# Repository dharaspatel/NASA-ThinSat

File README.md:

# NASA-ThinSat
---

This GitHub is a collection of 1) pcb design and logic 2) location determination 3) event triggering for mission NG13. 3 satellites will be launched - Joe Loftus, Burt Cour-Palais, Bill Rochelle. For more detail, see the GitHub Wiki.

--- 
## Joe Loftus 

Joe (also named *Cosmic DC*) has an Atmega, clock, power, and downlink capability. It keeps track of time to trigger melt wires to activate launchers and pyrolysis.

---
## Burt Cour-Palais

Burt (also named *Lt. Surge*) executes pyrolysis and launches the 4 launchers at the command of Joe. It also collects data on pyrolysis using the temperature sensor and CMOS image sensor.

---
## Bill Rochelle

Bill (also named *Fall Out Boy*), unlike Burt, has its own clock, Atmega, and downlink capability. In the next mission Bill will prove it *can* deorbit by executing all protocalls without propelant to deorbit.

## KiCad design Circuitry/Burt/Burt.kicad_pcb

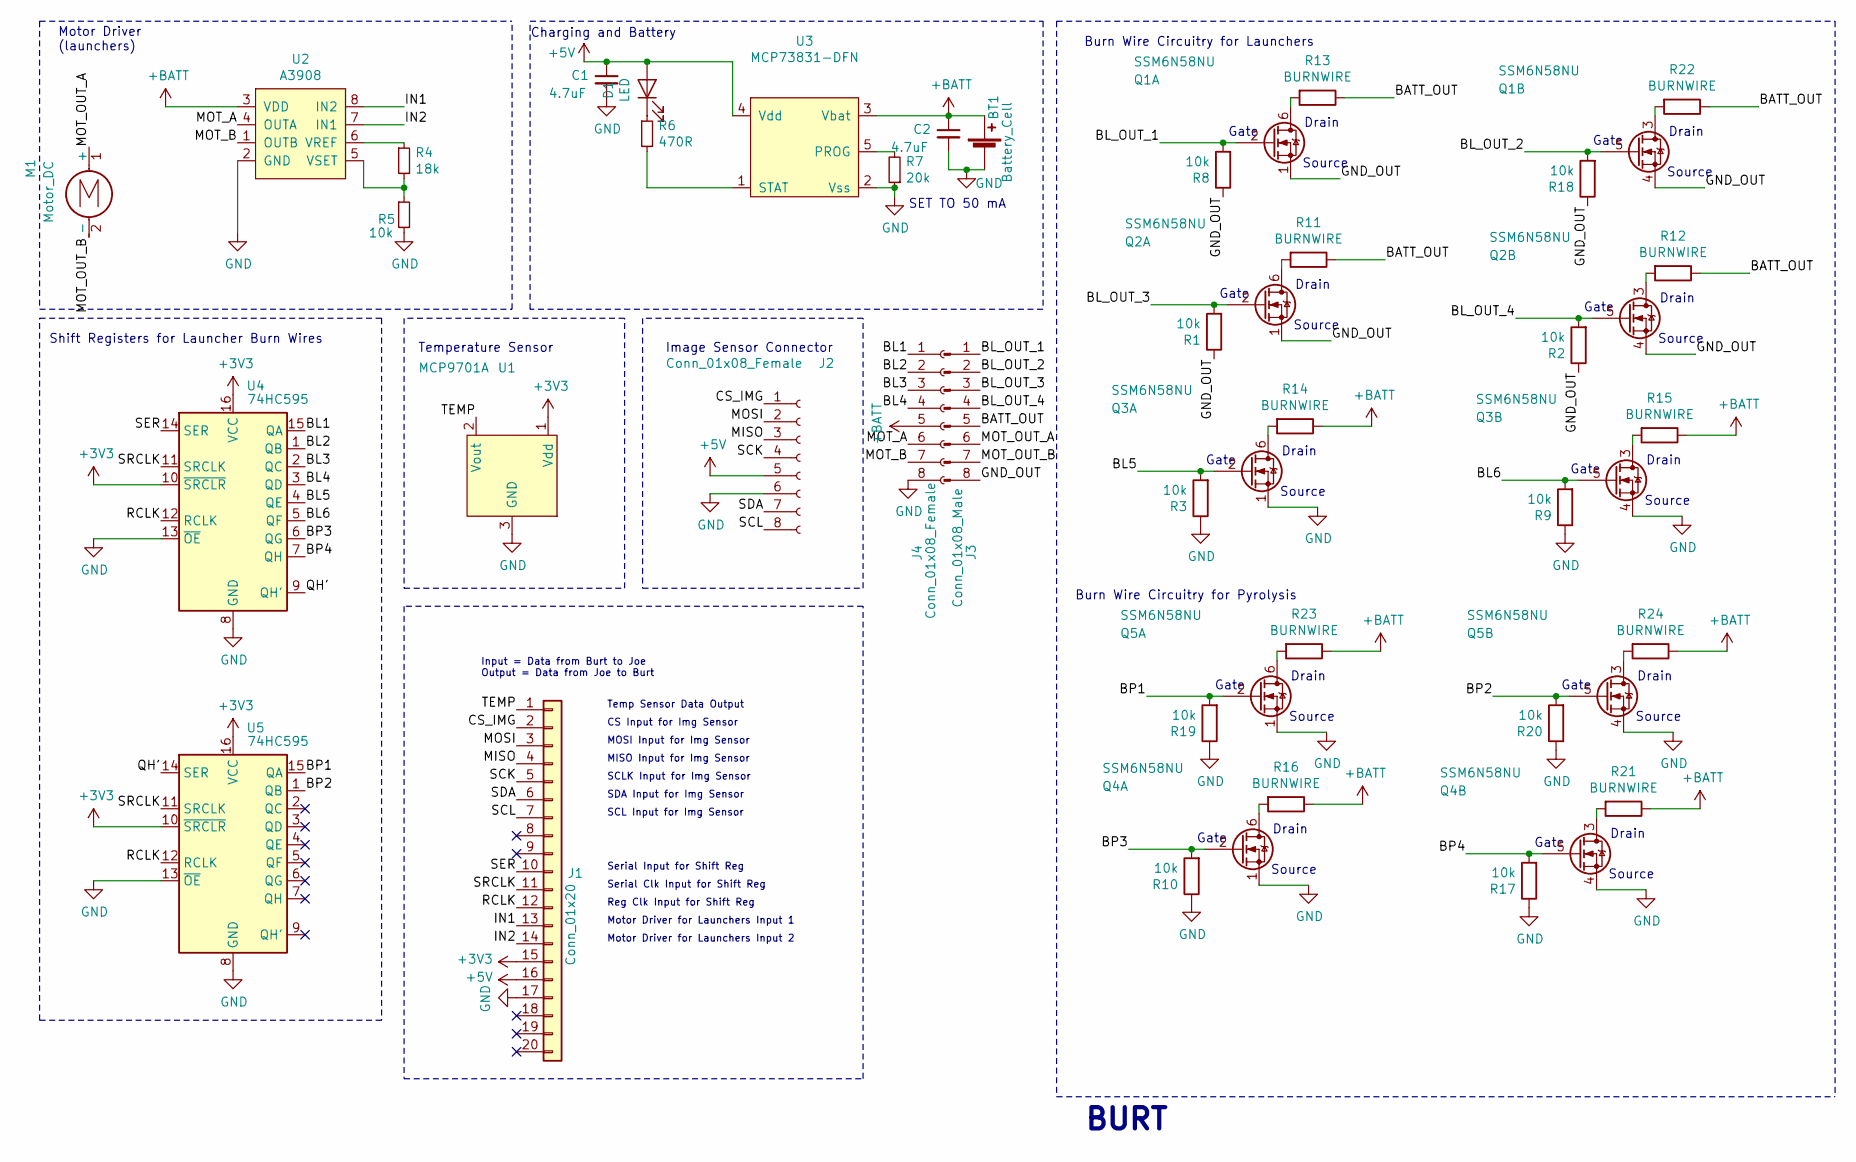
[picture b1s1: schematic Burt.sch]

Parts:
BT1: Battery_Cell; JST_PH_B2B-PH-K_1x02_P2.00mm_Vertical
C1, C2: 4.7uF; C_0603_1608Metric
D1: LED; LED_0603_1608Metric
J1: Conn_01x20; 62674-201121ALF
J2: Conn_01x08_Female; PinHeader_1x08_P2.54mm_Horizontal
J3: Conn_01x08_Male; PinHeader_1x08_P1.00mm_Vertical
J4: Conn_01x08_Female; PinHeader_1x08_P1.00mm_Vertical
M1: Motor_DC; JST_PH_B2B-PH-K_1x02_P2.00mm_Vertical
Q1, Q2, Q3, Q4, Q5: SSM6N58NU; DFN-6-1EP_2x2mm_P0.65mm_EP1x1.6mm
R1, R2, R3, R5, R8, R9, R10, R17, R18, R19, R20: 10k; R_0603_1608Metric
R4: 18k; R_0603_1608Metric
R6: 470R; R_0603_1608Metric
R7: 20k; R_0603_1608Metric
R11, R12, R13, R14, R15, R16, R21, R22, R23, R24: BURNWIRE; PinHeader_1x02_P1.00mm_Vertical
U1: MCP9701A; SOT-23
U2: A3908
U3: MCP73831-DFN; SOT-23-5
U4, U5: 74HC595; SOIC-16_3.9x9.9mm_P1.27mm

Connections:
+3V3: J1.15, U1.1 (Vdd), U4.10 (~SRCLR), U4.16 (VCC), U5.10 (~SRCLR), U5.16 (VCC)
+5V: C1.1, D1.2 (A), J1.16, J2.5, U3.4 (Vdd)
+BATT: BT1.1 (+), C2.1, J4.5, R14.1, R15.1, R16.1, R21.1, R23.1, R24.1, U2.3 (VDD), U3.3 (Vbat)
/BATT_OUT: J3.5, R11.1, R12.1, R13.1, R22.1
/BL1: J4.1, U4.15 (QA)
/BL2: J4.2, U4.1 (QB)
/BL3: J4.3, U4.2 (QC)
/BL4: J4.4, U4.3 (QD)
/BL5: Q3.2 (G), R3.2, U4.4 (QE)
/BL6: Q3.5 (G), R9.2, U4.5 (QF)
/BL_OUT_1: J3.1, Q1.2 (G), R8.2
/BL_OUT_2: J3.2, Q1.5 (G), R18.2
/BL_OUT_3: J3.3, Q2.2 (G), R1.2
/BL_OUT_4: J3.4, Q2.5 (G), R2.2
/BP1: Q5.2 (G), R19.2, U5.15 (QA)
/BP2: Q5.5 (G), R20.2, U5.1 (QB)
/BP3: Q4.2 (G), R10.2, U4.6 (QG)
/BP4: Q4.5 (G), R17.2, U4.7 (QH)
/CS_IMG: J1.2, J2.1
/GND_OUT: J3.8, Q1.1 (S), Q1.4 (S), Q2.1 (S), Q2.4 (S), R1.1, R2.1, R8.1, R18.1
/IN1: J1.13, U2.8 (IN2)
/IN2: J1.14, U2.7 (IN1)
/MISO: J1.4, J2.3
/MOSI: J1.3, J2.2
/MOT_A: J4.6, U2.4 (OUTA)
/MOT_B: J4.7, U2.1 (OUTB)
/MOT_OUT_A: J3.6, M1.1 (+)
/MOT_OUT_B: J3.7, M1.2 (-)
/QH': U4.9 (QH'), U5.14 (SER)
/RCLK: J1.12, U4.12 (RCLK), U5.12 (RCLK)
/SCK: J1.5, J2.4
/SCL: J1.7, J2.8
/SDA: J1.6, J2.7
/SER: J1.10, U4.14 (SER)
/SRCLK: J1.11, U4.11 (SRCLK), U5.11 (SRCLK)
/TEMP: J1.1, U1.2 (Vout)
GND: BT1.2 (-), C1.2, C2.2, J1.17, J2.6, J4.8, Q3.1 (S), Q3.4 (S), Q4.1 (S), Q4.4 (S), Q5.1 (S), Q5.4 (S), R3.1, R5.2, R7.1, R9.1, R10.1, R17.1, R19.1, R20.1, U1.3 (GND), U2.2 (GND), U3.2 (Vss), U4.8 (GND), U4.13 (~OE), U5.8 (GND), U5.13 (~OE)
unnamed: D1.1 (K), R6.1
unnamed: Q1.3 (D), R22.2
unnamed: Q1.6 (D), R13.2
unnamed: Q2.3 (D), R12.2
unnamed: Q2.6 (D), R11.2
unnamed: Q3.3 (D), R15.2
unnamed: Q3.6 (D), R14.2
unnamed: Q4.3 (D), R21.2
unnamed: Q4.6 (D), R16.2
unnamed: Q5.3 (D), R24.2
unnamed: Q5.6 (D), R23.2
unnamed: R4.1, U2.6 (VREF)
unnamed: R4.2, R5.1, U2.5 (VSET)
unnamed: R6.2, U3.1 (STAT)
unnamed: R7.2, U3.5 (PROG)

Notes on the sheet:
BURT
Temperature Sensor
SET TO 50 mA
Charging and Battery
Motor Driver (launchers)
Image Sensor Connector
Temp Sensor Data Output
CS Input for Img Sensor
MOSI Input for Img Sensor
Serial Input for Shift Reg
Serial Clk Input for Shift Reg
Reg Clk Input for Shift Reg
Motor Driver for Launchers Input 1
Motor Driver for Launchers Input 2
Input = Data from Burt to Joe Output = Data from Joe to Burt
MISO Input for Img Sensor
SCLK Input for Img Sensor
SDA Input for Img Sensor
SCL Input for Img Sensor
Burn Wire Circuitry for Launchers
Shift Registers for Launcher Burn Wires
Source
Gate
Drain
Burn Wire Circuitry for Pyrolysis

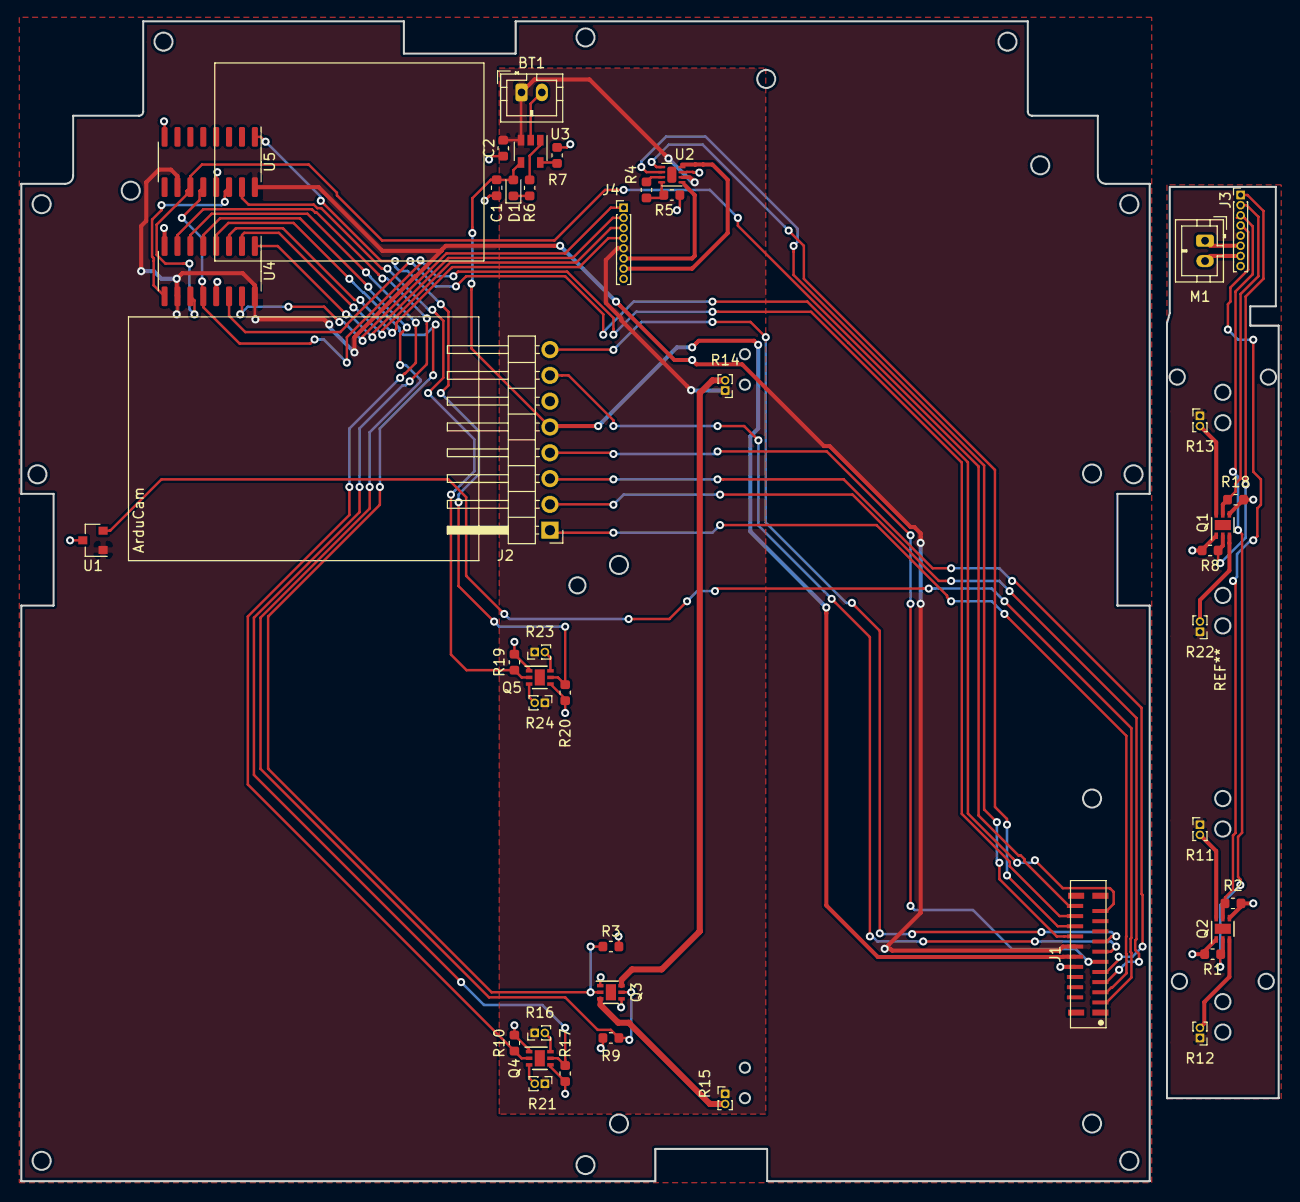
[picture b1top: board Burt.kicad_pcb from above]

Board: 2 copper layers, 123.8 x 114.2 mm, 43 parts (0 on the bottom side), 52 nets.

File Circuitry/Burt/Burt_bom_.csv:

Component,Description,Part,References,Value,Footprint,Quantity Per PCB,Datasheet,Part URL
1,Single-cell battery,Battery_Cell,BT1,Battery_Cell,JST_PH_B2B-PH-K_1x02_P2.00mm_Vertical,1,~,https://www.digikey.com/product-detail/en/jst-sales-america-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
2,"Unpolarized capacitor, small symbol",C_Small,C1 C2,4.7uF,C_0603_1608Metric,2,~,https://www.digikey.com/product-detail/en/samsung-electro-me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
3,Light emitting diode,LED,D1,LED,LED_0603_1608Metric,1,~,https://www.digikey.com/product-detail/en/lumex-opto-compone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
4,"Generic connector, single row, 01x04, script generated (kicad-library-utils/schlib/autogen/connector/)",Conn_01x04_Female,J2,Conn_01x04_Female,PinHeader_1x04_P2.54mm_Horizontal,1,~,https://www.digikey.com/product-detail/en/sullins-connector-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
5,"Generic connector, single row, 01x08, script generated (kicad-library-utils/schlib/autogen/connector/)",Conn_01x08_Female,J4,Conn_01x08_Female,PinHeader_1x08_P1.00mm_Vertical,1,~,
6,"Generic connector, single row, 01x08, script generated (kicad-library-utils/schlib/autogen/connector/)",Conn_01x08_Male,J3,Conn_01x08_Male,PinHeader_1x08_P1.00mm_Vertical,1,~,
7,"Generic connector, single row, 01x20, script generated (kicad-library-utils/schlib/autogen/connector/)",Conn_01x20,J1,Conn_01x20,62674-201121ALF,1,~,https://www.digikey.com/product-detail/en/amphenol-icc-fci/6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
8,DC Motor,Motor_DC,M1,Motor_DC,JST_PH_B2B-PH-K_1x02_P2.00mm_Vertical,1,~,https://www.pololu.com/product/4790/
9,2 N-MOSFET transistor,SSM6N58NU,Q1 Q2 Q3 Q4 Q5 Q6,SSM6N58NU,DFN-6-1EP_2x2mm_P0.65mm_EP1x1.6mm,6,,https://www.digikey.com/product-detail/en/toshiba-semiconduc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
10,Resistor,R,R1 R2 R3 R5 R8 R9 R10 R17 R18 R19 R20 R25 R27,10k,R_0603_1608Metric,13,~,https://www.digikey.com/product-detail/en/yageo/RT0603BRD071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
11,"Resistor, small symbol",R_Small,R4,18k,R_0603_1608Metric,1,~,https://www.digikey.com/product-detail/en/yageo/RT0603BRD071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
12,"Resistor, small symbol",R_Small,R7,20k,R_0603_1608Metric,1,~,https://www.digikey.com/product-detail/en/yageo/RC0603FR-072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
13,"Resistor, small symbol",R_Small,R6,470R,R_0603_1608Metric,1,~,https://www.digikey.com/product-detail/en/yageo/RC0603FR-074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
14,Resistor,R,R11 R12 R13 R14 R15 R16 R21 R22 R23 R24 R26 R28,BURNWIRE,PinHeader_1x02_P1.00mm_Vertical,12,~,
15,8-bit serial in/out Shift Register 3-State Outputs,74HC595,U4 U5,74HC595,SOIC-16_3.9x9.9mm_P1.27mm,2,http://www.ti.com/lit/ds/symlink/sn74hc595.pdf,https://www.digikey.com/product-detail/en/nexperia-usa-inc/7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
16,,A3908-Custom,U2,A3908,A3908,1,,https://www.digikey.com/product-detail/en/allegro-microsyste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
17,,MCP73831-DFN-Custom,U3,MCP73831-DFN,SOT-23-5,1,,https://www.digikey.com/product-detail/en/microchip-technolo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
18,,MCP9701A-Custom,U1,MCP9701A,SOT-23,1,http://ww1.microchip.com/downloads/en/DeviceDoc/20001942G.pdf,https://www.digikey.com/product-detail/en/microchip-technolo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





Component Groups:,18
Component Count:,48
Fitted Components:,48
Number of PCBs:,1
Total components:,48
Schematic Version:,
Schematic Date:,
PCB Variant:,['default']
BoM Date:,Tue 30 Jul 2019 11:10:57 AM EDT
Schematic Source:,/home/dpatel1/NASA-ThinSat/Circuitry/Burt/Burt.sch
KiCad Version:,Eeschema 5.1.2-f72e74a~84~ubuntu18.04.1

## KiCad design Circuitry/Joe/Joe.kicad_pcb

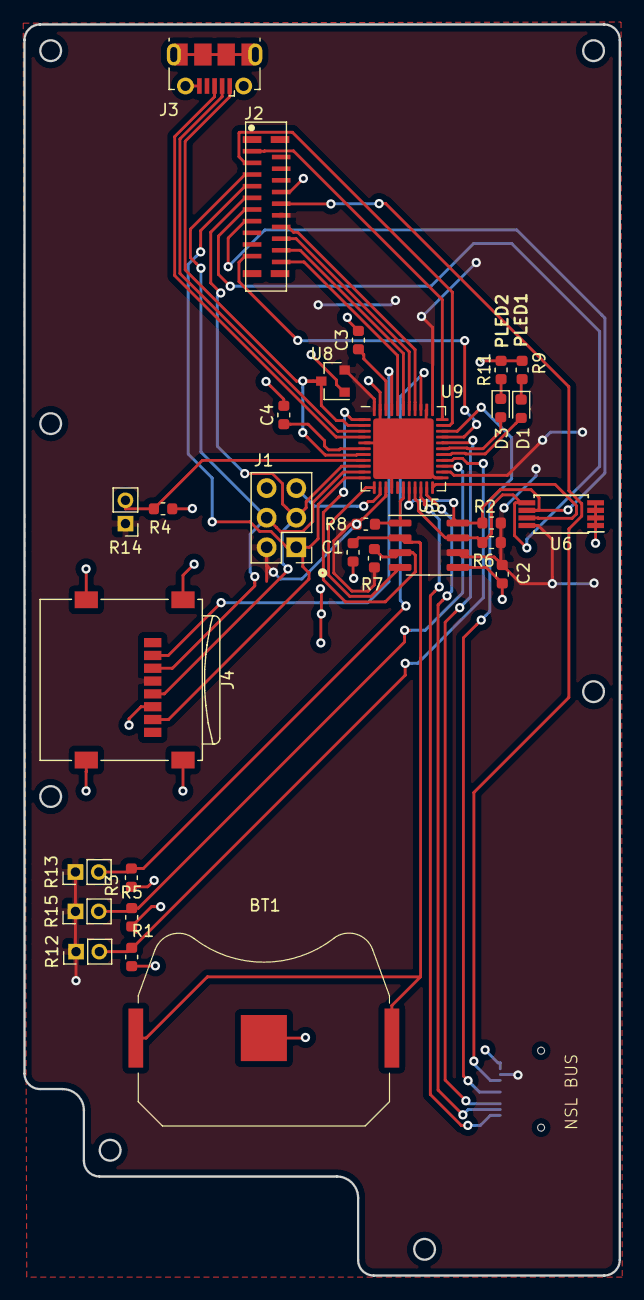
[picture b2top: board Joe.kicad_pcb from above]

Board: 2 copper layers, 51.1 x 107.3 mm, 30 parts (1 on the bottom side), 39 nets.

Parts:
BT1: Battery_Cell; BatteryHolder_Keystone_3034_1x20mm
C1, C2: 0.1uF; C_0603_1608Metric
C3, C4: 1uF; C_0603_1608Metric
D1, D3: LED; LED_0603_1608Metric
J1: Conn_02x03_Counter_Clockwise; PinHeader_2x03_P2.54mm_Vertical
J2: Conn_01x20; 62674-201121ALF
J3: USB_B_Micro; USB_Micro-B_Molex-105017-0001
J4: Micro_SD_Card; microSD_HC_Wuerth_693072010801
R1, R3, R4, R5: 1k; R_0603_1608Metric
R2, R6, R7, R8: 10k; R_0603_1608Metric
R9, R11: 440R; R_0603_1608Metric
R12, R13, R14, R15: R_PHOTO; PinHeader_1x02_P2.00mm_Vertical
U5: DS3231MZ; SOIC-8_3.9x4.9mm_P1.27mm
U6: M24C32-XDW5TP; TSSOP-8_4.4x3mm_P0.65mm
U7: DF12-20DS; DF12-20DS-0.5V(86)
U8: AP2127N-3.3; SOT-23
U9: ATmega32U4-MU; QFN-44-1EP_7x7mm_P0.5mm_EP5.2x5.2mm

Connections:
+3V3: C2.1, J1.2, J2.15, J4.4, R2.1, R6.1, R7.1, R8.1, R12.1, R13.1, R14.1, R15.1, U5.6, U6.8, U7.18, U8.2, U9.14, U9.24, U9.34, U9.44
+5V: J2.16, U7.17
/BUSY: U7.13, U9.29
/CRYSTAL: R8.2, U5.1, U9.17
/CS_IMG: J2.2, U9.32
/D+: J3.3, U9.4
/D-: J3.2, U9.3
/IN1: J2.13, U9.38
/IN2: J2.14, U9.37
/MISO: J1.1, J2.4, J4.7, U9.11
/MOSI: J1.4, J2.3, J4.3, U9.10
/PHO1: R1.1, R12.2, U9.26
/PHO2: R3.1, R13.2, U9.36
/PHO3: R4.1, R14.2, U9.8
/PHO4: R5.1, R15.2, U9.25
/PLED1: D1.2, U9.27
/PLED3: D3.2, U9.28
/RCLK: J2.12, U9.39
/RST: J1.5, U9.13
/RX: U7.12, U9.21
/SCK: J1.3, J2.5, J4.5, U9.9
/SCL: J2.7, R2.2, U5.8, U6.6, U9.18
/SDA: J2.6, R6.2, U5.7, U6.5, U9.19
/SER: J2.10, U9.30
/SQW: R7.2, U5.3, U9.1
/SRCLK: J2.11, U9.40
/STBY: U7.15, U9.31
/TEMP: J2.1, U9.33
/TMR_RST: U5.4, U9.12
/TX: U7.11, U9.20
/VBUS: J3.1, U8.3, U9.2, U9.7
/WC: U6.7, U9.22
/~CS_SD: J4.2, U9.41
GND: BT1.2, C1.2, C2.2, C3.2, C4.2, J1.6, J2.17, J3.5, J3.6, J4.6, J4.9, R1.2, R3.2, R4.2, R5.2, R9.2, R11.2, U5.5, U6.1, U6.2, U6.3, U6.4, U7.19, U7.20, U8.1, U9.5, U9.15, U9.23, U9.35, U9.43, U9.45
unnamed: BT1.1, C1.1, U5.2
unnamed: C3.1, U9.42
unnamed: C4.1, U9.6
unnamed: D1.1, R9.1
unnamed: D3.1, R11.1

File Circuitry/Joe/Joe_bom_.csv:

Component,Description,Part,References,Value,Footprint,Quantity Per PCB,Datasheet,Part URL
1,Single-cell battery,Battery_Cell,BT1,Battery_Cell,BatteryHolder_Keystone_3034_1x20mm,1,~,https://www.digikey.com/product-detail/en/keystone-electroni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
2,"Polarized capacitor, small symbol",CP_Small,C1,0.1uF,C_0603_1608Metric,1,~,https://www.digikey.com/product-detail/en/knowles-syfer/0603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
3,"Unpolarized capacitor, small symbol",C_Small,C2,0.1uF,C_0603_1608Metric,1,~,https://www.digikey.com/product-detail/en/knowles-syfer/0603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
4,Unpolarized capacitor,C,C3 C4,1uF,C_0603_1608Metric,2,~,https://www.digikey.com/product-detail/en/murata-electronics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
5,Light emitting diode,LED,D1,LED,LED_0603_1608Metric,1,~,https://www.digikey.com/product-detail/en/lite-on-inc/LTST-C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
6,"Generic connector, single row, 01x20, script generated (kicad-library-utils/schlib/autogen/connector/)",Conn_01x20,J2,Conn_01x20,62674-201121ALF,1,~,
7,"Generic connector, double row, 02x03, counter clockwise pin numbering scheme (similar to DIP packge numbering), script generated (kicad-library-utils/schlib/autogen/connector/)",Conn_02x03_Counter_Clockwise,J1,Conn_02x03_Counter_Clockwise,PinHeader_2x03_P2.54mm_Vertical,1,~,https://www.digikey.com/product-detail/en/sullins-connector-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
8,Micro SD Card Socket,Micro_SD_Card,J4,Micro_SD_Card,microSD_HC_Wuerth_693072010801,1,http://katalog.we-online.de/em/datasheet/693072010801.pdf,https://www.digikey.com/product-detail/en/wurth-electronics-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
9,USB Micro Type B connector,USB_B_Micro,J3,USB_B_Micro,USB_Micro-B_Molex-105017-0001,1,~,https://www.digikey.com/product-detail/en/molex/1050170001/W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
10,Resistor,R,R2 R6 R7 R8,10k,R_0603_1608Metric,4,~,https://www.digikey.com/product-detail/en/yageo/RT0603BRD071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
11,Resistor,R,R1 R3 R4 R5,1k,R_0603_1608Metric,4,~,https://www.digikey.com/product-detail/en/yageo/RT0603DRD071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
12,Resistor,R,R9,440R,R_0603_1608Metric,1,~,https://www.digikey.com/product-detail/en/yageo/RC0603FR-074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
13,Photoresistor,R_PHOTO,R12 R13 R14 R15,R_PHOTO,PinHeader_1x02_P2.00mm_Vertical,4,~,https://www.digikey.com/product-detail/en/advanced-photonix/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
14,"300mA low dropout linear regulator, shutdown pin, 2.5V-6V input voltage, 3.3V fixed positive output, SOT-23 package",AP2127N-3.3,U8,AP2127N-3.3,SOT-23,1,https://www.diodes.com/assets/Datasheets/AP2127.pdf,https://www.digikey.com/product-detail/en/diodes-incorporate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
15,"16MHz, 32kB Flash, 2.5kB SRAM, 1kB EEPROM, USB 2.0, QFN-44",ATmega32U4-MU,U9,ATmega32U4-MU,QFN-44-1EP_7x7mm_P0.5mm_EP5.2x5.2mm,1,http://ww1.microchip.com/downloads/en/DeviceDoc/Atmel-7766-8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,https://www.digikey.com/product-detail/en/microchip-technolo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
16,,DF12-20DS-Custom,U7,DF12-20DS,DF12-20DS-0.5V(86),1,,https://www.digikey.com/product-detail/en/hirose-electric-co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
17,"±5ppm, I2C Real-Time Clock SOIC-8",DS3231MZ,U5,DS3231MZ,SOIC-8_3.9x4.9mm_P1.27mm,1,http://datasheets.maximintegrated.com/en/ds/DS3231M.pdf,https://www.digikey.com/product-detail/en/maxim-integrated/D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
18,,UFDFPN8-MC-Custom,U6,M24C32-XDW5TP,TSSOP-8_4.4x3mm_P0.65mm,1,https://www.st.com/content/ccc/resource/technical/document/d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,https://www.digikey.com/product-detail/en/stmicroelectronics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
19,,SN74LVC1G3157DCKR,U1 U2,SN74LVC1G3157DCKR,DCK6,2,,





Component Groups:,19
Component Count:,30
Fitted Components:,30
Number of PCBs:,1
Total components:,30
Schematic Version:,
Schematic Date:,
PCB Variant:,['default']
BoM Date:,Tue 30 Jul 2019 11:13:57 AM EDT
Schematic Source:,/home/dpatel1/NASA-ThinSat/Circuitry/Joe/Joe.sch
KiCad Version:,Eeschema 5.1.2-f72e74a~84~ubuntu18.04.1

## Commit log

2019-06-12 Set up general strucutre for communicating with the payload (receiving data from sensors and sending it to the NSL Bus)
2019-06-20 organization and sensor byte addition
2019-06-24 Added spectrometer, photodiode, and atmega to sch
2019-06-27 Began writing code for electronics on Joe and Bill satellites
2019-06-28 A bit of file organization and division into Joe, Burt, Bill satellites
2019-07-01 Pinouts for sensors on burt and calc_state
2019-07-01 bus sensor pins and additional circuitry
2019-07-09 sch review changes, eeprom, linear image sensor.
2019-07-10 Complete with for-loops
2019-07-10 battery and burn wire circuitry, motor driver *incomplete
2019-07-10 motor driver
2019-07-10 burt for review
2019-07-10 Fixed symbol libraries
2019-07-10 Changed burt some
2019-07-10 changes to Joe: part lables, BW, and shift regs
2019-07-10 burt screw terminals fixed, img sensor conn
2019-07-10 screw terminal on joe
2019-07-10 Added SD card reader
2019-07-10 shift reg to burt
2019-07-10 fixed up joe
2019-07-11 Joe: RTC changed to soic8, added labels to screw terminal, removed shift regs Burt: added shift reg
2019-07-11 complete screw terminal, labeling, etc. done for FINAL REVIEW
2019-07-11 part URLs for Joe Loftus
2019-07-11 Added part URLs
2019-07-11 joe done for final review
2019-07-11 Fixed Garbage
2019-07-11 urls
2019-07-11 burt organization and screw terminal and image sensor connector
2019-07-11 fixed burn wire circuits
2019-07-12 Added custom footprint library
2019-07-12 electrical rules check ran and corrected
2019-07-12 footprints for burt
2019-07-12 Got footprints for Cosmic DC
2019-07-12 joe footprints, symbols, and sch reviewed
2019-07-12 Fixed some garbage
2019-07-15 Made a new ribbon cable connector
2019-07-15 Made cosmic dc outline
2019-07-15 joe layout
2019-07-16 completed joe layout for review; addresses for dcf
2019-07-17 Did lt surge
2019-07-17 Made pour more rectangular
2019-07-17 complete joe layoutgit add .git add .git add . woooohooooooo!
2019-07-17 functions for rtc, nsl bus, sd card, read photocells
2019-07-18 Finshed lt surge layout
2019-07-18 Moved ribbon connector
2019-07-18 planet on pcb!
2019-07-18 Sharing is caring, Emma.
    I put Emma's files into the public domain where they _belong_. Information wants to be free. Now all will know the truth.
2019-07-18 Build Lt. Surge
2019-07-18 Build zip for joe
2019-07-18 Pants are relative
    I replaced the absolute filepaths with relative ones so that other people can run it now.
2019-07-18 Keep it going
    I fixed the longitude fitting. I also changed a bunch of variable names and added comments as I was working through it.
2019-07-18 Wait… that's not even close!
    I did some analysis to find out that the current fit system gets to be over 450 km off. That's too much. I'm going to start looking into a residuals system.
2019-07-19 functions on burt
2019-07-19 bill schematic
2019-07-19 Relativity is a conspiracy
    I changed it to deal with residuals instead of absolute coordinates. The fit functions for longitude and altitude had to change. The fit still doesn't work super well. I suspect that the assumption t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
2019-07-19 Still garbage
    I gave the regression full control over all parameters. Still not a great fit. Probably because we need at least three inputs to get a semblance of linearity, and in particular, not ones that are pra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
2019-07-22 Once is enough
    I made it convert the epoch from string to datetime when it loads it instead of every time it uses it.
2019-07-22 I officially hate statsmodels
    If you want to fit a dataframe, you call statsmodels.formula.api.ols().
    If you want to fit an ndarray, you call statsmodels.api.OLS().
    This is scudding Python. What in Davy Jones's Locker is the matter with this package?
    I also changed it to fit to three dependent variables instead of two, because two wasn't enough. Give me a hot sec to make sure those independent variables are actually dece.
2019-07-23 Numpy is a gift
    I replaced all the list and things with numpy arrays to make it nicer and just a little bit faster.
2019-07-23 Eigenvectors.
    I did some informal PCA and found some values that are decently independent (read: still highly correlated) to use for predicting location. I'm going to try to fix the fitting now and see how it goes.
2019-07-23 Approximating intelligence
    The sunwend code was bugging me, so I made it better. Now, if an apparent "night" lasts fewer than 10 seconds, it will ignore it completely. It's much less error prone this way. At least in theory. W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
2019-07-23 It is remarkably nonlinear
    The word of today was validation. I wrote some new code to properly fit the estimation on a simulation that wasn't used in the regression. Turns out the phase shift and other sine parameters aren't l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
2019-07-23 image processing
2019-07-23 Splines!
    I changed the fit curves to splines. Splines are great.
2019-07-24 script to run many gmat scripts
    python script to run multiple gmat scripts with slightly different initial velocity vector
2019-07-24 GMAT script to find lat, long, alt at each sunrise
2019-07-24 You suck.
    I did some proper validation, and it turns out to actually be pretty good.
2019-07-24 Now with less cheating!
    It was using data it wouldn't actually have access to yet. Now it doesn't do that, and it still works fine.
2019-07-24 Packaged and ready to go
    It outputs a file now.
2019-07-24 I like this one better
2019-07-25 Don't trust anyone
    I changed it so that it no longer depends on the absolute accuracy of the RTC; it can guess its position given only the difference between times. Altitude is a lot harder this way, but latitude and l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
2019-07-25 Revert "Don't trust anyone"
    This reverts commit 63708b5009fe73210ad0e3231a94a75da33f998c.
2019-07-25 Okay, but just one
    I realized that we actually need the clock to be accurate for the residual computation thing to work at all. So we'll need to be correcting it as we go, anyway. Oh, well.
    That's why I reverted the last commit. This one is to fix a bug I fixed in the commit I just reverted.
2019-07-25 getTime, calcState, organization, etc.
2019-07-26 As far as I can remember
    I made it more general; it now uses all of the sunrise and sunset times back to a given memory point. This will make it easier to account for more degrees of freedom in the input errors.
2019-07-26 Adding multiplexing
2019-07-26 Changed camera one more time
2019-07-26 Time for you to get a watch!
    I taught it not to trust the absolute value of its RTC, and in fact to correct its own RTC's errors. It's pretty impressive. I'm so proud.
2019-07-26 bus, mag, motor drivers
2019-07-29 integration of read photocells
2019-07-29 burnwire arduino code
2019-07-29 determine when an eclipse is moonless
2019-07-30 add comments to find moonless
2019-07-30 Milliseconds.
    I did three things.
    - I added and accounted for error in the sunwend time measurement. The fit is way worse now, but that's the reality we have. I'm thinking of ways to add more memories without leaving it in the dark f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
    - I changed the fitting to take place over the expected orbit times rather than the actual ones, such that the value of the fit is not _completely_ at the mercy of the error on the last sunrise measu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
    - I refactored the position estimating code because this is getting confusing and I want to make absolutely sure I'm not using information that the spacecraft wouldn't know.
2019-07-30 Amnesia is no excuse
    I made it able to guess its position even when it hasn't hit NUM_MEMORIES orbits. It really doesn't need all of them; its initial guesses aren't actually _that_ bad.
2019-07-30 More accurate distributions
    It helps to know the data you expect.
2019-07-30 BOM stuff and a ton of programming
2019-07-30 I broke it.
    I added the location finding function. It doesn't work yet. Ha.
2019-07-31 get moon location
2019-07-31 Rename loadkernel.txt to Programming/location_timing/loadkernel.txt
2019-07-31 Rename moonephemeris.py to Programming/location_timing/moonephemeris.py
2019-08-01 Multiple launch dates
    I modified it to work with multiple launch dates. It was pretty easy.
2019-08-01 Did a review on Joe.c
2019-08-01 That is not my job
    I found a library to handle the spline stuff I had ignored before, and wrote a simple linear interpolation routine to go with it.
2019-08-01 Yeah, that'll probably work.
    I fleshed it out slightly more. And integrated the sunwend detection.
2019-08-02 puts moon pos in txt file
2019-08-02 save moon pos and time to txt file
2019-08-02 added threshold for moonless
2019-08-02 Corrected critical error
2019-08-02 change initial pos and v
2019-08-05 I'm to young to die!
    I started looking into penultimate orbit stuff. I need much better simulations than the ones Emma gave me, though.
2019-08-05 Emma, I hate your indices
    The 101 report files thing was weird. Also, I made the variable names more specific and enabled velocity and position to have different scales.
2019-08-05 Almost functional
    I redid all of the absolute paths so that I could actually run it, and fixed the fact that this script was pointing at a completely wrong input script. I also simplified the output file specification.
2019-08-05 Removed outdated syntax
    How did this even get here?
2019-08-05 Removed most of code
    This isn't actually needed anymore...
2019-08-05 It's a drag race
    I told it to vary its drag area as well as initial conditions. I also made my syntax better and added print statements.
2019-08-05 Very Important Change
2019-08-06 Yes, GMAT, I wanted you to _actually_ run it.
    I can't believe you need to specify to GMAT that you want it to run the script instead of just "interpreting" it and that you want it to exit when it's done instead of blocking your terminal indefini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
2019-08-06 Joe.C
2019-08-06 WAIT
    I forgot an important piece.
2019-08-06 Declaring dependence
    I made a dependencies folder and started searching for some of these headers that Dhara's been referencing.
2019-08-06 I missed one
2019-08-06 Take them, Dhara! You've already taken everything else!
    I got the location finding to work with deorbiting and also with multiple launch dates.
2019-08-07 We might be able to actually do this
    I worked out the graphs, and it looks like penultimate orbits are actually pretty discinct from final ones.
2019-08-07 Started periferal branch
2019-08-07 All hail Facebook
    I got more data.
2019-08-07 comment fixes
2019-08-07 So Dashing!
    That readSD function was real wacky.
2019-08-07 I NEED IT
    These dependencies don't work.
2019-08-07 Justin, you are late to the party
2019-08-08 This is my side
    I drew a line between the anteantepenultimate and anteanteantepenultimate orbits.
2019-08-08 Do it for me, please
    I found a dependency for reading SD cards that I think might actually work.
2019-08-08 The magic of Windows
    I did a thing with Atmel studio to make a new testing script.
2019-08-08 PDDCPINDDDDCDBPRC
    It didn't have a pin layout for this one. I wonder what I'm doing.
2019-08-08 Why is there only a 6 and 7?
    I missed a couple.
2019-08-09 Add Eric's Sunset Detector
    It's not ready to be on the satellite yet, but with some work this fall it may become ready.
2019-08-09 EEprom library working for byte read and write
